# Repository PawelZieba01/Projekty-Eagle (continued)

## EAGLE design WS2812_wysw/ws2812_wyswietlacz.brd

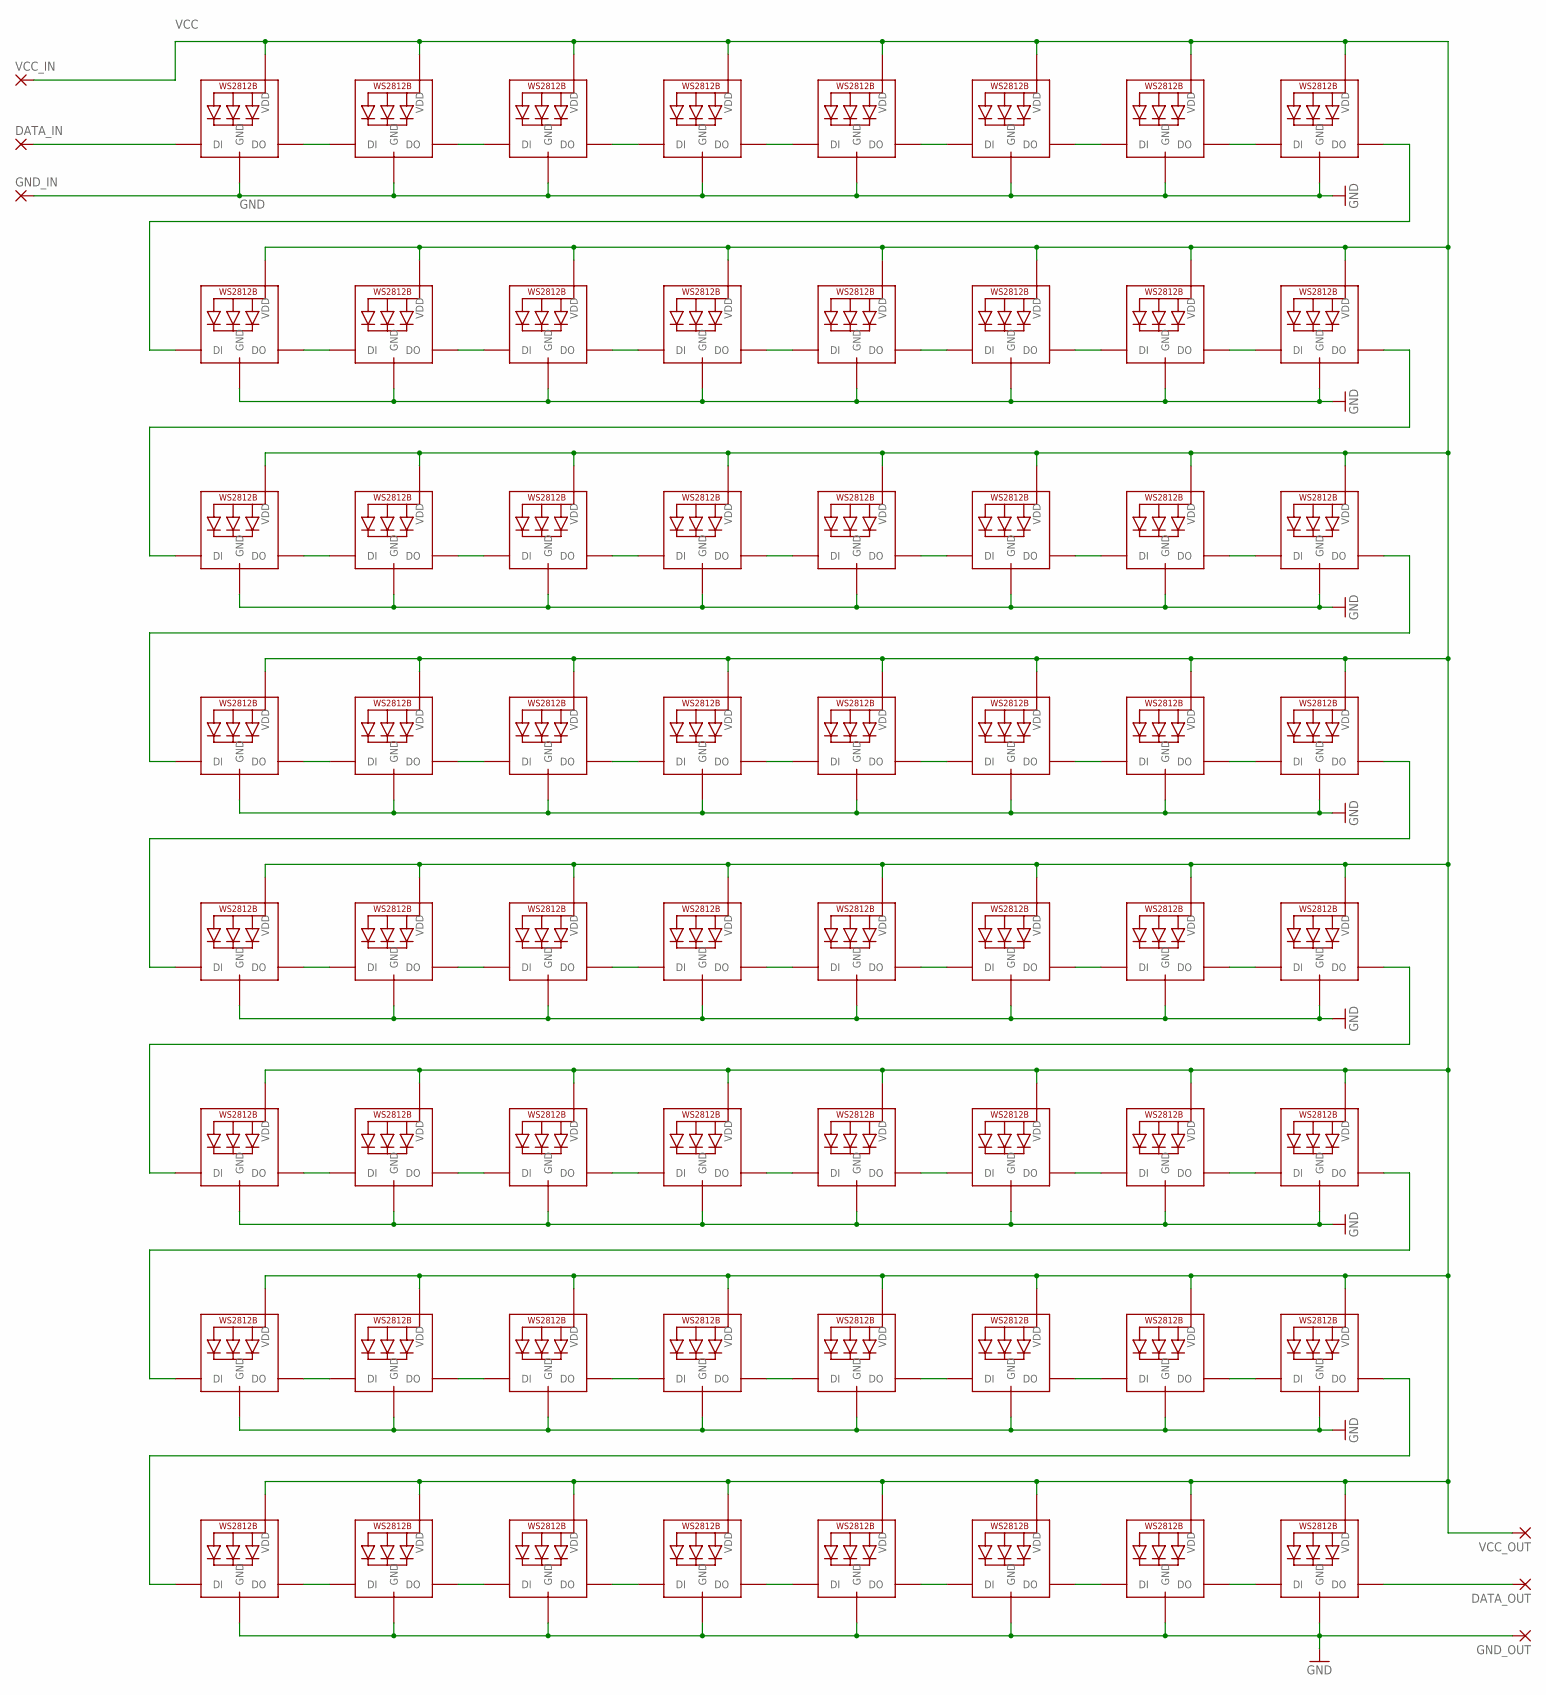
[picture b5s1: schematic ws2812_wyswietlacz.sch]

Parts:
DATA_IN: 2,54/1,0
DATA_OUT: 2,54/1,0
GND_IN: 2,54/1,0
GND_OUT: 2,54/1,0
LED1, LED2, LED3, LED4, LED5, LED6, LED7, LED8, LED9, LED10, LED11, LED12, LED13, LED14, LED15, LED16, LED17, LED18, LED19, LED20, LED21, LED22, LED23, LED24, LED25, LED26, LED27, LED28, LED29, LED30, LED31, LED32, LED33, LED34, LED35, LED36, LED37, LED38, LED39, LED40, LED41, LED42, LED43, LED44, LED45, LED46, LED47, LED48, LED49, LED50, LED51, LED52, LED53, LED54, LED55, LED56, LED57, LED58, LED59, LED60, LED61, LED62, LED63, LED64: WS2812B_5050N; WS2812B-NARROW
VCC_IN: 2,54/1,0
VCC_OUT: 2,54/1,0

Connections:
GND: GND_IN.1, GND_OUT.1, LED1.3-GND (GND), LED2.3-GND (GND), LED3.3-GND (GND), LED4.3-GND (GND), LED5.3-GND (GND), LED6.3-GND (GND), LED7.3-GND (GND), LED8.3-GND (GND), LED9.3-GND (GND), LED10.3-GND (GND), LED11.3-GND (GND), LED12.3-GND (GND), LED13.3-GND (GND), LED14.3-GND (GND), LED15.3-GND (GND), LED16.3-GND (GND), LED17.3-GND (GND), LED18.3-GND (GND), LED19.3-GND (GND), LED20.3-GND (GND), LED21.3-GND (GND), LED22.3-GND (GND), LED23.3-GND (GND), LED24.3-GND (GND), LED25.3-GND (GND), LED26.3-GND (GND), LED27.3-GND (GND), LED28.3-GND (GND), LED29.3-GND (GND), LED30.3-GND (GND), LED31.3-GND (GND), LED32.3-GND (GND), LED33.3-GND (GND), LED34.3-GND (GND), LED35.3-GND (GND), LED36.3-GND (GND), LED37.3-GND (GND), LED38.3-GND (GND), LED39.3-GND (GND), LED40.3-GND (GND), LED41.3-GND (GND), LED42.3-GND (GND), LED43.3-GND (GND), LED44.3-GND (GND), LED45.3-GND (GND), LED46.3-GND (GND), LED47.3-GND (GND), LED48.3-GND (GND), LED49.3-GND (GND), LED50.3-GND (GND), LED51.3-GND (GND), LED52.3-GND (GND), LED53.3-GND (GND), LED54.3-GND (GND), LED55.3-GND (GND), LED56.3-GND (GND), LED57.3-GND (GND), LED58.3-GND (GND), LED59.3-GND (GND), LED60.3-GND (GND), LED61.3-GND (GND), LED62.3-GND (GND), LED63.3-GND (GND), LED64.3-GND (GND)
unnamed: DATA_IN.1, LED1.4-DIN (DI)
unnamed: DATA_OUT.1, LED64.2-DOUT (DO)
unnamed: LED1.2-DOUT (DO), LED2.4-DIN (DI)
unnamed: LED2.2-DOUT (DO), LED3.4-DIN (DI)
unnamed: LED3.2-DOUT (DO), LED4.4-DIN (DI)
unnamed: LED4.2-DOUT (DO), LED5.4-DIN (DI)
unnamed: LED5.2-DOUT (DO), LED6.4-DIN (DI)
unnamed: LED6.2-DOUT (DO), LED7.4-DIN (DI)
unnamed: LED7.2-DOUT (DO), LED8.4-DIN (DI)
unnamed: LED8.2-DOUT (DO), LED9.4-DIN (DI)
unnamed: LED9.2-DOUT (DO), LED10.4-DIN (DI)
unnamed: LED10.2-DOUT (DO), LED11.4-DIN (DI)
unnamed: LED11.2-DOUT (DO), LED12.4-DIN (DI)
unnamed: LED12.2-DOUT (DO), LED13.4-DIN (DI)
unnamed: LED13.2-DOUT (DO), LED14.4-DIN (DI)
unnamed: LED14.2-DOUT (DO), LED15.4-DIN (DI)
unnamed: LED15.2-DOUT (DO), LED16.4-DIN (DI)
unnamed: LED16.2-DOUT (DO), LED17.4-DIN (DI)
unnamed: LED17.2-DOUT (DO), LED18.4-DIN (DI)
unnamed: LED18.2-DOUT (DO), LED19.4-DIN (DI)
unnamed: LED19.2-DOUT (DO), LED20.4-DIN (DI)
unnamed: LED20.2-DOUT (DO), LED21.4-DIN (DI)
unnamed: LED21.2-DOUT (DO), LED22.4-DIN (DI)
unnamed: LED22.2-DOUT (DO), LED23.4-DIN (DI)
unnamed: LED23.2-DOUT (DO), LED24.4-DIN (DI)
unnamed: LED24.2-DOUT (DO), LED25.4-DIN (DI)
unnamed: LED25.2-DOUT (DO), LED26.4-DIN (DI)
unnamed: LED26.2-DOUT (DO), LED27.4-DIN (DI)
unnamed: LED27.2-DOUT (DO), LED28.4-DIN (DI)
unnamed: LED28.2-DOUT (DO), LED29.4-DIN (DI)
unnamed: LED29.2-DOUT (DO), LED30.4-DIN (DI)
unnamed: LED30.2-DOUT (DO), LED31.4-DIN (DI)
unnamed: LED31.2-DOUT (DO), LED32.4-DIN (DI)
unnamed: LED32.2-DOUT (DO), LED33.4-DIN (DI)
unnamed: LED33.2-DOUT (DO), LED34.4-DIN (DI)
unnamed: LED34.2-DOUT (DO), LED35.4-DIN (DI)
unnamed: LED35.2-DOUT (DO), LED36.4-DIN (DI)
unnamed: LED36.2-DOUT (DO), LED37.4-DIN (DI)
unnamed: LED37.2-DOUT (DO), LED38.4-DIN (DI)
unnamed: LED38.2-DOUT (DO), LED39.4-DIN (DI)
unnamed: LED39.2-DOUT (DO), LED40.4-DIN (DI)
unnamed: LED40.2-DOUT (DO), LED41.4-DIN (DI)
unnamed: LED41.2-DOUT (DO), LED42.4-DIN (DI)
unnamed: LED42.2-DOUT (DO), LED43.4-DIN (DI)
unnamed: LED43.2-DOUT (DO), LED44.4-DIN (DI)
unnamed: LED44.2-DOUT (DO), LED45.4-DIN (DI)
unnamed: LED45.2-DOUT (DO), LED46.4-DIN (DI)
unnamed: LED46.2-DOUT (DO), LED47.4-DIN (DI)
unnamed: LED47.2-DOUT (DO), LED48.4-DIN (DI)
unnamed: LED48.2-DOUT (DO), LED49.4-DIN (DI)
unnamed: LED49.2-DOUT (DO), LED50.4-DIN (DI)
unnamed: LED50.2-DOUT (DO), LED51.4-DIN (DI)
unnamed: LED51.2-DOUT (DO), LED52.4-DIN (DI)
unnamed: LED52.2-DOUT (DO), LED53.4-DIN (DI)
unnamed: LED53.2-DOUT (DO), LED54.4-DIN (DI)
unnamed: LED54.2-DOUT (DO), LED55.4-DIN (DI)
unnamed: LED55.2-DOUT (DO), LED56.4-DIN (DI)
unnamed: LED56.2-DOUT (DO), LED57.4-DIN (DI)
unnamed: LED57.2-DOUT (DO), LED58.4-DIN (DI)
unnamed: LED58.2-DOUT (DO), LED59.4-DIN (DI)
unnamed: LED59.2-DOUT (DO), LED60.4-DIN (DI)
unnamed: LED60.2-DOUT (DO), LED61.4-DIN (DI)
unnamed: LED61.2-DOUT (DO), LED62.4-DIN (DI)
unnamed: LED62.2-DOUT (DO), LED63.4-DIN (DI)
unnamed: LED63.2-DOUT (DO), LED64.4-DIN (DI)
VCC: LED1.1-VDD (VDD), LED2.1-VDD (VDD), LED3.1-VDD (VDD), LED4.1-VDD (VDD), LED5.1-VDD (VDD), LED6.1-VDD (VDD), LED7.1-VDD (VDD), LED8.1-VDD (VDD), LED9.1-VDD (VDD), LED10.1-VDD (VDD), LED11.1-VDD (VDD), LED12.1-VDD (VDD), LED13.1-VDD (VDD), LED14.1-VDD (VDD), LED15.1-VDD (VDD), LED16.1-VDD (VDD), LED17.1-VDD (VDD), LED18.1-VDD (VDD), LED19.1-VDD (VDD), LED20.1-VDD (VDD), LED21.1-VDD (VDD), LED22.1-VDD (VDD), LED23.1-VDD (VDD), LED24.1-VDD (VDD), LED25.1-VDD (VDD), LED26.1-VDD (VDD), LED27.1-VDD (VDD), LED28.1-VDD (VDD), LED29.1-VDD (VDD), LED30.1-VDD (VDD), LED31.1-VDD (VDD), LED32.1-VDD (VDD), LED33.1-VDD (VDD), LED34.1-VDD (VDD), LED35.1-VDD (VDD), LED36.1-VDD (VDD), LED37.1-VDD (VDD), LED38.1-VDD (VDD), LED39.1-VDD (VDD), LED40.1-VDD (VDD), LED41.1-VDD (VDD), LED42.1-VDD (VDD), LED43.1-VDD (VDD), LED44.1-VDD (VDD), LED45.1-VDD (VDD), LED46.1-VDD (VDD), LED47.1-VDD (VDD), LED48.1-VDD (VDD), LED49.1-VDD (VDD), LED50.1-VDD (VDD), LED51.1-VDD (VDD), LED52.1-VDD (VDD), LED53.1-VDD (VDD), LED54.1-VDD (VDD), LED55.1-VDD (VDD), LED56.1-VDD (VDD), LED57.1-VDD (VDD), LED58.1-VDD (VDD), LED59.1-VDD (VDD), LED60.1-VDD (VDD), LED61.1-VDD (VDD), LED62.1-VDD (VDD), LED63.1-VDD (VDD), LED64.1-VDD (VDD), VCC_IN.1, VCC_OUT.1

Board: 2 copper layers, 70 parts (0 on the bottom side), 67 nets, no tracks yet.

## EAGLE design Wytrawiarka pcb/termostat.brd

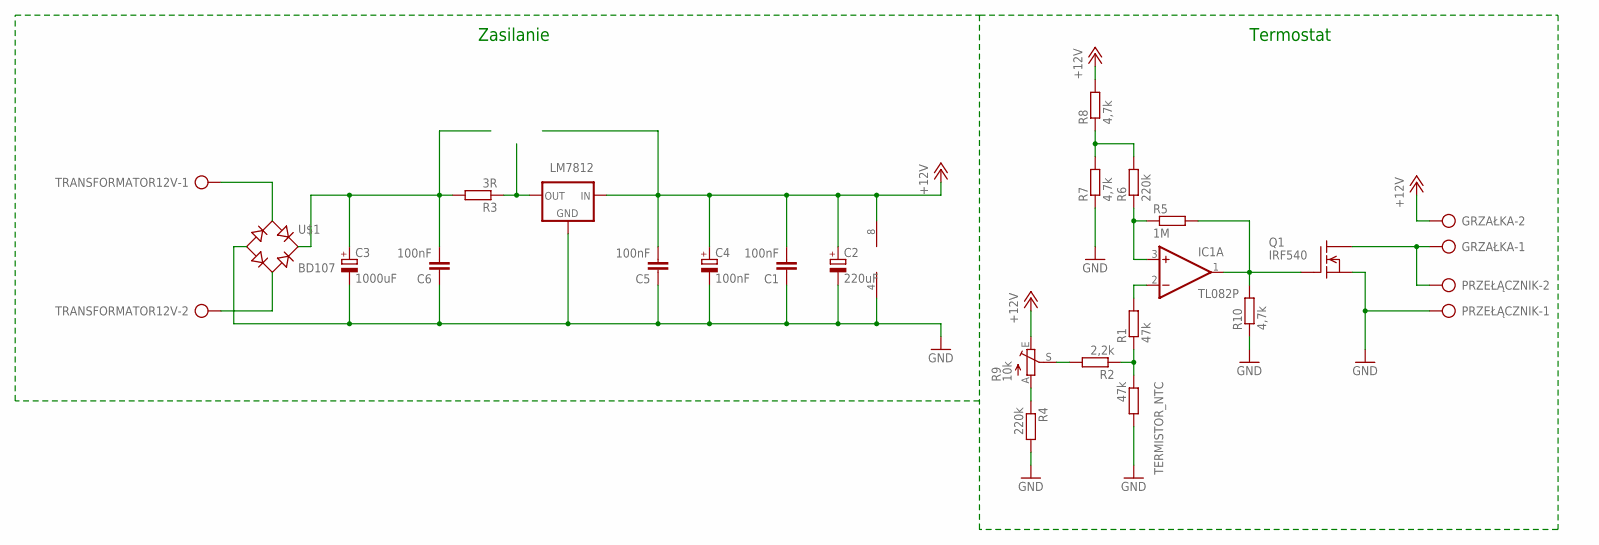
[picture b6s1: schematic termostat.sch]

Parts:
C1, C5, C6: 100nF; C50-45-75
C2: 220uF; E2,5-6
C3: 1000uF; E5-13
C4: 100nF; E2,5-6
GRZAŁKA: AK300/2
IC1: TL082P; DIL08
LM7812: 79XXS
PRZEŁĄCZNIK: AK300/2
Q1: IRF540; TO220
R1: 47k; 204/7
R2: 2,2k; 204/7
R3: 3R; 204/7
R4, R6: 220k; 204/7
R5: 1M; 204/7
R7, R8, R10: 4,7k; 204/7
R9: 10k; CA6V
TERMISTOR_NTC: 47k; 204/7
TRANSFORMATOR12V: AK300/2
U$1: BD107; B-DIL

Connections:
+12V: C1.P$2 (2), C2.P$1 (+), C4.P$1 (+), C5.P$2 (2), GRZAŁKA.2, IC1.8 (V+), LM7812.IN, R8.P$2 (2), R9.E
GND: C1.P$1 (1), C2.P$2 (-), C3.P$2 (-), C4.P$2 (-), C5.P$1 (1), C6.P$1 (1), IC1.4 (V-), LM7812.GND, PRZEŁĄCZNIK.1, Q1.3 (S), R4.P$2 (2), R7.P$1 (1), R10.P$1 (1), TERMISTOR_NTC.P$2 (2), U$1.-
unnamed: R6.P$2 (2), R7.P$2 (2), R8.P$1 (1)
unnamed: IC1.3 (+IN), R5.P$1 (1), R6.P$1 (1)
unnamed: IC1.1 (OUT), Q1.1 (G), R5.P$2 (2), R10.P$2 (2)
unnamed: GRZAŁKA.1, PRZEŁĄCZNIK.2, Q1.2 (D)
unnamed: IC1.2 (-IN), R1.P$2 (2)
unnamed: R2.P$2 (2), R9.S
unnamed: R1.P$1 (1), R2.P$1 (1), TERMISTOR_NTC.P$1 (1)
unnamed: R4.P$1 (1), R9.A
unnamed: TRANSFORMATOR12V.1, U$1.AC1
unnamed: TRANSFORMATOR12V.2, U$1.AC2
unnamed: C3.P$1 (+), C6.P$2 (2), R3.P$2 (2), U$1.+
unnamed: LM7812.OUT, R3.P$1 (1)

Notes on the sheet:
Zasilanie
Termostat

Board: 2 copper layers, 24 parts (0 on the bottom side), 14 nets, no tracks yet.
